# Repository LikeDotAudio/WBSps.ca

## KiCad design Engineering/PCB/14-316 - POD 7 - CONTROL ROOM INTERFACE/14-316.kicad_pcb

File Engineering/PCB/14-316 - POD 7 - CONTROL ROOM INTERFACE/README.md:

# 14-316 - POD 7 - CONTROL ROOM INTERFACE

**POD 7 - CONTROL ROOM INTERFACE**

Converted to KiCad from `WBSps Engineering from H drive/WBSps - POD_OLD/POD7/ISS1/TANGO/14-316.PCB` (tango).

| Components | Pads | Track segments | Vias | Pours |
|---|---|---|---|---|
| 119 | 444 | 866 | 0 | 15 |

Nets: from `WBSps Engineering from H drive/WBSps - POD_OLD/POD7/ISS1/ORCAD/POD7.NET`.

Other copies of the same file:

- `wbsPS-NOT UPLOADED/WBSps - POD_OLD-20221115T024220Z-001/WBSps - POD_OLD/POD7/ISS1/TANGO/14-316.PCB`
- `WBSps Engineering from H drive-20261018T013433Z-1-002/WBSps Engineering from H drive/WBSps - POD_OLD/POD7/ISS1/TANGO/14-316.PCB`

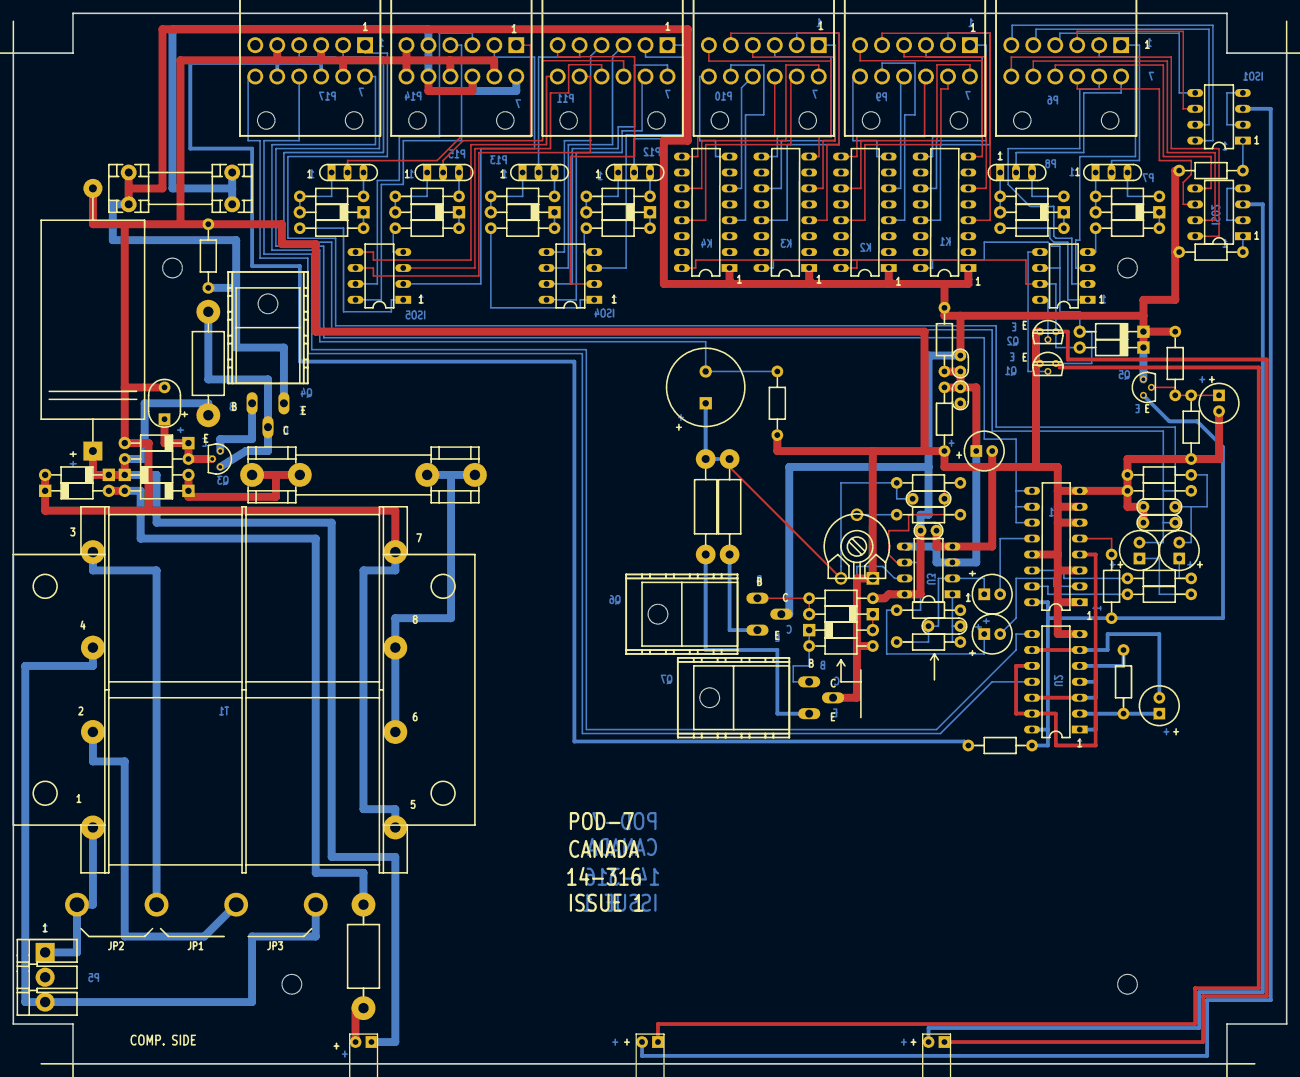
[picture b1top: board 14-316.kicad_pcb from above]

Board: 2 copper layers, 203.2 x 167.6 mm, 119 parts (0 on the bottom side), 133 nets.

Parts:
C1: 10/35; TANTB.2
C2: 1000/63; EC165
C3, C4, C17: 22/25; RAD.1
C5, C6: 1000P; CAP.2
C7, C8, C9, C10: 47/25; RAD.1
C11, C12: 22P; CAP.2
C13, C15, C16: 0.1; CAP.1
C14: 1000/25; E1000R25P
D1, D2, D3, D4, D5, D6, D7, D8, D10, D11, D12, D13, D14, D15: 1N4003; DO-41
D9: 1N4748; DO-41
DS1: RED; 551LED
DS2, DS3: YELLOW; 551LED
F1: 0.5A; AGC
F2: 0.5A; 217
FF2: BTITLE
ISO1, ISO2, ISO3, ISO4, ISO5: ILD-1; DIP8
K1, K2, K3, K4: RZ-24W-C; DIP16
P1, P2, P3, P4: 1502-2; LUG
P5: CE156F22-3; PAN3/156
P6, P9, P10, P11, P14, P17: SLD 3.5/6/90G; WEID12/138
P7, P8, P12, P13, P15, P16: 929705-01-03; SIP3
Q1, Q2: 2N6731; TO-237
Q3, Q5: 2N3904; TO-92
Q4, Q6: TIP29B; TO-220HS
Q7: TIP30B; TO-220HS
R1, R3, R11, R13, R15, R17, R22, R33, R34: 10K; R1/4
R2, R4, R12, R14, R16, R18: 1K5; R1/4
R5, R6: 2K2; R1/4
R7: 50 3W; R03WE
R8, R19: 15K; R1/4
R9: 10K 3W; R03WE
R10: 22K; R1/4
R20: 4K7; R1/4
R21: 1K; R1/4
R23: 620; R1/4
R24, R25, R37: 100K; R1/4
R26, R27: 16K2; R1/4
R28, R29: 4K75; R1/4
R30: 2K; R1/4
R31: 12K; R1/4
R32: 5K; PT10V
R35, R36: 30 1W; R01MF
R38, R39: 10K 1%; R1/4
T1: 229C56
U1: 74HC4053; DIP16
U2: 74HC132; DIP14
U3: NE5532N; DIP8
W1: TITLE
X1, X2, X3, X4: 4-40SCREW

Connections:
+5V: Q5.1, R21.2, R23.2, U1.16, U2.14
GND: C1.2, C2.2, C3.2, C5.2, C6.2, C16.2, C17.2, D9.2, DS1.1, P14.6, P14.8, P14.10, P14.12, P17.3, P17.5, P17.8, Q1.1, Q2.1, Q7.2, R10.2, R20.2, R24.1, R25.1, R32.1, R34.2, R37.2, R39.2, U1.1, U1.3, U1.6, U1.7, U1.8, U1.13, U2.7, U3.4
ISOA1+: ISO1.6, P6.3
ISOA1-: ISO1.5, P6.4
ISOA2+: ISO1.7, P6.5
ISOA2-: ISO1.8, P6.6
ISOB1+: ISO3.6, P6.9
ISOB1-: ISO3.5, P6.10
ISOB2+: ISO3.7, P6.11
ISOB2-: ISO3.8, P6.12
N00001: ISO2.3, P6.2
N00002: D3.2, DS2.1, ISO2.6, K1.16, K3.16, Q1.3
N00003: K1.11, P9.1
N00004: K1.13, P9.2
N00005: K1.9, P9.3
N00006: K3.11, P10.1
N00007: K1.6, P9.4
N00008: K3.13, P10.2
N00009: K1.4, P9.5
N00010: K3.9, P10.3
N00011: K1.8, P9.6
N00012: K3.6, P10.4
N00013: P7.3, R1.1
N00014: P6.1, P7.2
N00015: D1.2, P7.1, R1.2
N00016: ISO2.5, Q1.2
N00017: K2.11, P9.7
N00018: K3.4, P10.5
N00019: K2.13, P9.8
N00020: K3.8, P10.6
N00021: K2.9, P9.9
N00022: K4.11, P10.7
N00023: K2.6, P9.10
N00024: K4.13, P10.8
N00025: D1.1, R2.1
N00026: ISO2.4, R2.2
N00027: K2.4, P9.11
N00028: K4.9, P10.9
N00029: K2.8, P9.12
N00030: K4.6, P10.10
N00031: K4.4, P10.11
N00032: P6.7, P8.2
N00033: K4.8, P10.12
N00034: ISO2.2, P6.8
N00035: D4.2, DS3.1, ISO2.7, K2.16, K4.16, Q2.3
N00036: P8.3, R3.1
N00037: D2.2, P8.1, R3.2
N00038: ISO2.8, Q2.2
N00039: D2.1, R4.1
N00040: ISO2.1, R4.2
N00041: DS2.2, ISO1.3
N00042: DS3.2, ISO3.3
N00043: ISO1.2, ISO1.4
N00044: ISO3.2, ISO3.4
N00045: ISO1.1, R5.2
N00046: ISO3.1, R6.2
N00047: ISO4.3, P11.2
N00048: ISO4.6, P11.3
N00049: ISO5.3, P11.10
N00050: ISO5.6, P11.11
N00051: P12.3, R11.1
N00052: P11.1, P12.2
N00053: D12.2, P12.1, R11.2
N00054: P15.3, R15.1
N00055: P11.9, P15.2
N00056: D11.2, P15.1, R15.2
N00057: ISO4.4, R12.2
N00058: ISO4.5, P11.4
N00059: ISO5.4, R16.2
N00060: ISO5.5, P11.12
N00061: P11.5, P13.2
N00062: D12.1, R12.1
N00063: D11.1, R16.1
N00064: ISO4.2, P11.6
N00065: ISO4.7, P11.7
N00066: ISO4.8, P11.8
N00067: ISO5.2, P14.2
N00068: ISO5.7, P14.3
N00069: P14.1, P16.2
N00070: ISO5.8, P14.4
N00071: F2.1, P14.5, P14.7, P14.9, P14.11
N00072: P13.3, R13.1
N00073: D13.2, P13.1, R13.2
N00074: P16.3, R17.1
N00075: D10.2, P16.1, R17.2
N00076: ISO4.1, R14.2
N00077: ISO5.1, R18.2
N00078: D13.1, R14.1
N00079: D10.1, R18.1
N00080: P1.1, P5.1, T1.1
N00083: D6.2, T1.5
N00084: D5.1, D6.1, F1.1
N00085: C2.1, F1.2, R7.1, R8.1, R9.2
N00086: Q3.3, Q4.2, R7.2
N00087: P2.1, T1.3
N00088: P3.1, T1.2
N00089: T1.6, T1.8
N00090: Q3.1, Q4.1
N00091: P4.1, P5.3, T1.4
N00092: C1.1, D9.1, Q3.2, R8.2
N00093: D5.2, T1.7
N00094: DS1.2, R9.1
N00095: C9.1, C11.1, R28.1, U3.2
N00096: C11.2, C12.1, R28.2, U3.1
N00097: C9.2, U1.12
N00098: C7.1, R26.1
N00099: C10.1, C13.1, R29.2, R30.1, R31.1, U3.6
N00102: C5.1, C7.2, P17.1, R24.2
N00103: R26.2, U1.14
N00104: C13.2, C14.1, R31.2, R32.3, R35.2, R36.2
N00105: R27.2, U1.15
N00106: D15.2, Q6.1, R33.2
N00107: C10.2, U1.2
N00108: U1.4, U2.10, U2.13
N00109: C12.2, R29.1
N00110: R21.1, U1.5
N00111: Q6.3, R35.1
N00112: C6.1, C8.2, P17.2, R25.2
N00113: C8.1, R27.1
N00114: D14.2, D15.1, U3.7
N00115: U1.9, U1.10, U1.11
N00116: C14.2, P17.7, R37.1
N00117: Q7.3, R36.1
N00118: D14.1, Q7.1, R34.1
N00120: P17.9, P17.11, R23.1
N00121: P17.10, U2.8
N00122: P17.12, U2.11
N00123: C3.1, Q5.2, R19.2, R20.1
N00124: R22.1, U2.3, U2.4, U2.5, U2.12
N00125: C4.2, U2.6, U2.9
N00126: C4.1, R22.2, U2.1, U2.2
V/2: C15.2, C16.1, C17.1, R38.2, R39.1, U3.3, U3.5
VCC: C15.1, D3.1, D4.1, F2.2, K1.1, K2.1, K3.1, K4.1, Q4.3, Q5.3, Q6.2, R5.1, R6.1, R10.1, R19.1, R33.1, R38.1, U3.8
